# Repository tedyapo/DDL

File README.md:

# DDL
Diode-Diode Logic hardware designs: digital logic using only common diodes

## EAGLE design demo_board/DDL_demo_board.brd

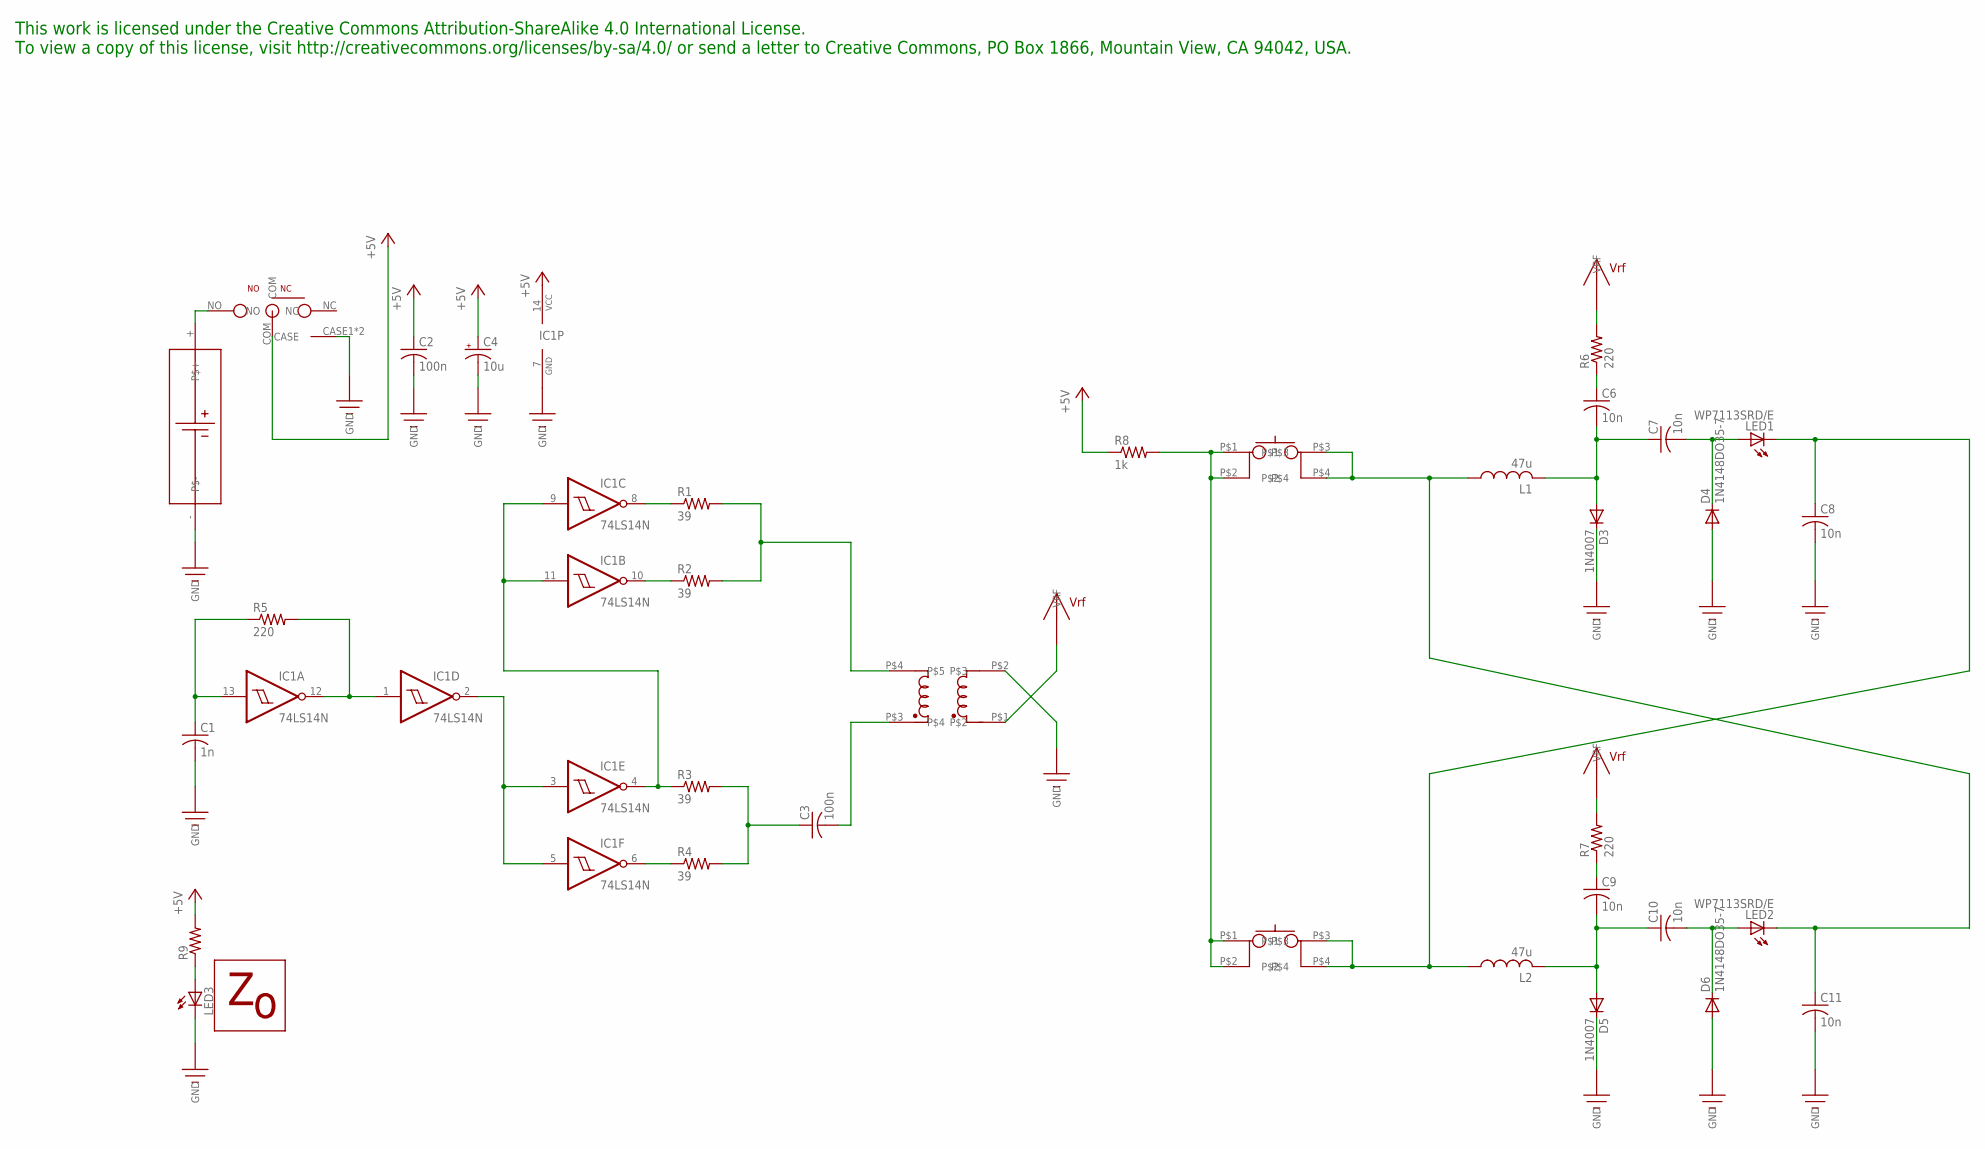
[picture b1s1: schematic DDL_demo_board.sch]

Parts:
C1: 1n; C025-025X050
C2, C3: 100n; C050-025X075
C4: 10u; E2,5-6
C6, C7, C8, C9, C10, C11: 10n; C025-025X050
D3, D5: 1N4007; DO41-10
D4, D6: 1N4148DO35-7; DO35-7
IC1: 74LS14N; DIL14
L1, L2: 47u; 0207/10
LED1, LED2: WP7113SRD/E; LED5MM
LED3: LEDP-LCC-2-BACK; P-LCC-2-TOPLED-RG
R1, R2, R3, R4: 39; 0207/10
R5, R6, R7: 220; 0207/10
R8: 1k; 0207/10
R9: R-US_R0805; R0805
U$1: Z0_LOGO200MIL_NS; Z0_LOGO_200_MIL_NO_SILK
U$2: OS1020_SPDT; OS1020_SWITCH
U$10, U$11: PCB_MOM_SPST_SWITCH; SWITCH_PCB_MOM
U$12: FT37_BIFILAR_1; FT37_BIFILAR_VERT2
U$16: 4AA_BATT_HOLDERNO_HOLES; 4AA_BATT_PACK_NO_HOLES

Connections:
+5V: C2.1, C4.+, IC1.14 (VCC), R8.1, R9.2, U$2.COM
GND: C1.2, C2.2, C4.-, C8.2, C11.2, D3.C, D4.A, D5.C, D6.A, IC1.7 (GND), LED3.C, U$2.CASE1 (CASE), U$2.CASE2 (CASE), U$12.P$2, U$16.-
unnamed: C3.2, U$12.P$3
unnamed: C7.2, D4.C, LED1.A
unnamed: C1.1, IC1.13 (I), R5.1
unnamed: IC1.2 (O), IC1.3 (I), IC1.5 (I)
unnamed: IC1.4 (O), IC1.9 (I), IC1.11 (I), R3.1
unnamed: C6.1, R6.1
unnamed: IC1.8 (O), R1.1
unnamed: IC1.10 (O), R2.1
unnamed: LED3.A, R9.1
unnamed: IC1.6 (O), R4.1
unnamed: C6.2, C7.1, D3.A, L1.2
unnamed: U$2.NO, U$16.+
unnamed: C3.1, R3.2, R4.2
unnamed: R1.2, R2.2, U$12.P$4
unnamed: C9.1, R7.1
unnamed: C9.2, C10.1, D5.A, L2.2
unnamed: C10.2, D6.C, LED2.A
unnamed: C11.1, L1.1, LED2.K (C), U$10.P$3, U$10.P$4
unnamed: IC1.1 (I), IC1.12 (O), R5.2
unnamed: C8.1, L2.1, LED1.K (C), U$11.P$3, U$11.P$4
unnamed: R8.2, U$10.P$1, U$10.P$2, U$11.P$1, U$11.P$2
VRF: R6.2, R7.2, U$12.P$1

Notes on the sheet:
This work is licensed under the Creative Commons Attribution-ShareAlike 4.0 International License. To view a copy of this license, visit http://creativecommons.org/licenses/by-sa/4.0/ or send a letter to Creative Commons, PO Box 1866, Mountain View, CA 94042, USA.

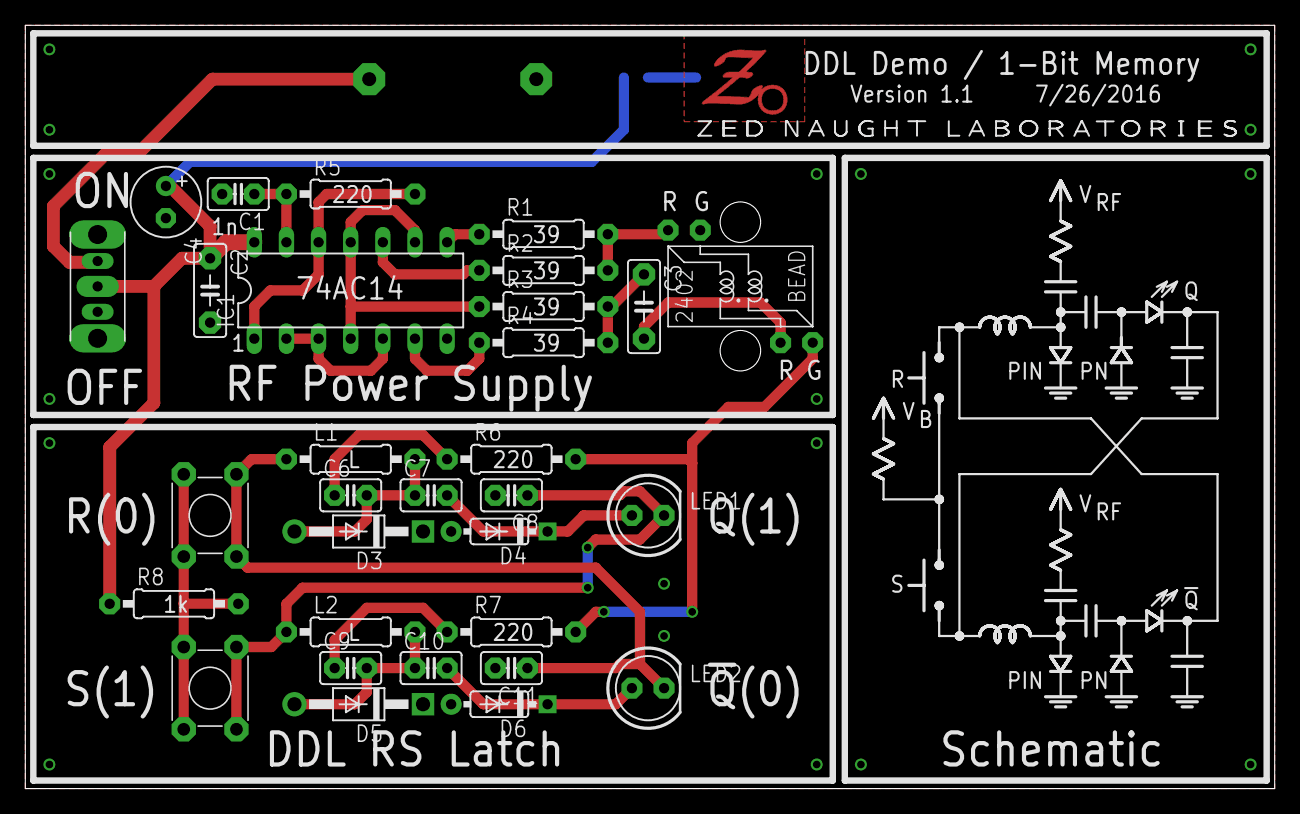
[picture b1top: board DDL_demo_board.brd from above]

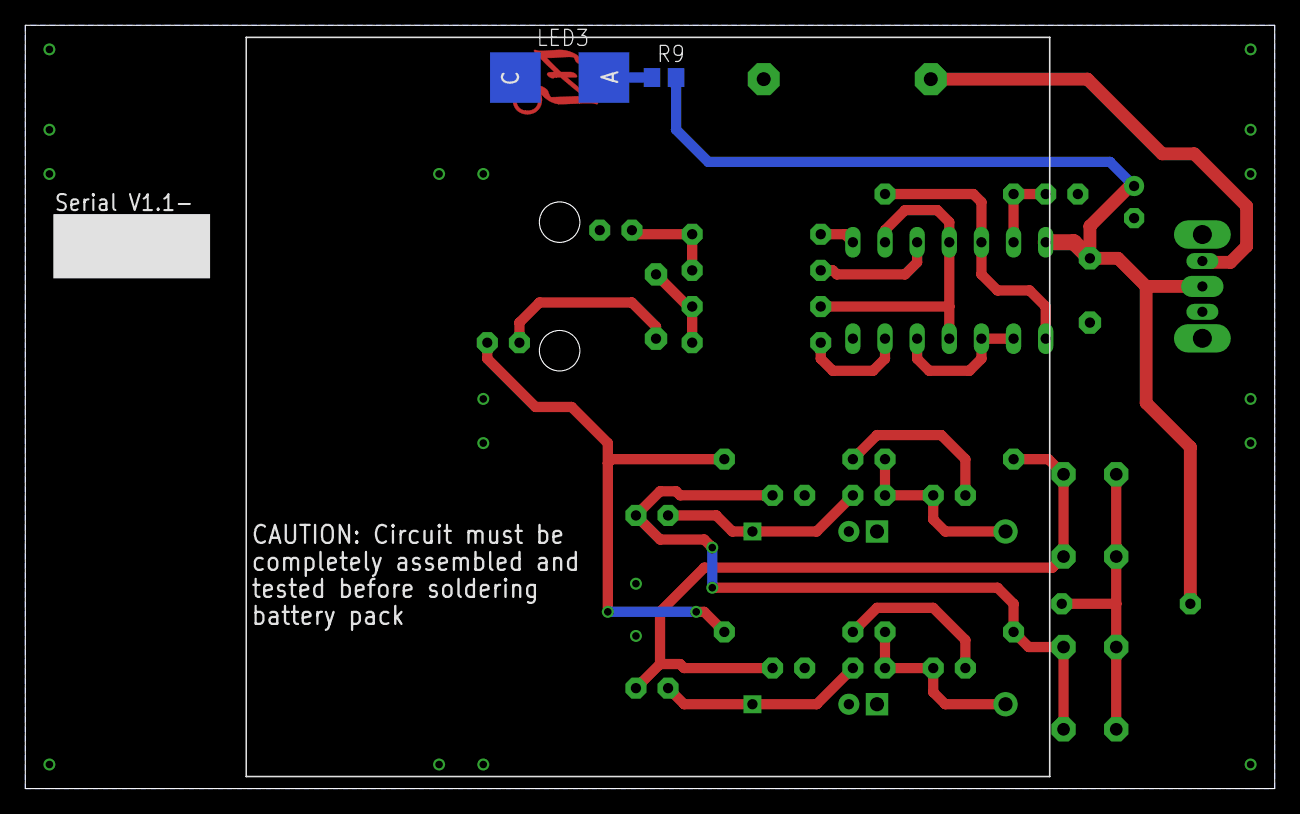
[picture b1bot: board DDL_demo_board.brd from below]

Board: 2 copper layers, 98.7 x 60.3 mm, 35 parts (3 on the bottom side), 24 nets.

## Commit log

2016-07-26 Demo board and license added baseline (V.0) demo board design added license file
2016-07-27 Updated demo board for new inductors * added gerbers to repository * added zip file script
